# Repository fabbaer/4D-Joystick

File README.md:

# 4D-Joystick

## Introduction
The 4D-Joystick allows people with physical disabilities to control complex RC-toys, like plains or multicopper. The RC-toys are controlled via a mouthpiece, a pressure sensor and movements of the head.

The system is divided into two units. The joystickunit is the user interface. It records the user inputs, processes them and forwards them to the remoteunit. The remoteunit is responsible for the communication with the RC-toy.

### Joystickunit
The joystickunit is the main part of the system and handles all user interactions. The heart of the system is a self-developed hardware with a Cortex-M4-Controller. The firmware offers a command-line-interface (CLI) via a USB connection to configure the system. Up to 32 different configurations can be stored on the joystickunit, each offering a flexible mapping of all inputs and outputs and configurations like deadzones. 

The joystickunit can either be powered via USB or via the remoteunit. All peripherals are placed inside a 3D-printed enclosure, which can be mounted on a stand. On the outside of the housing a display and a rotary button is placed, which can be used to load different configurations and display system information. Additionally, there are four headphone jacks to connect external buttons, which can be used to control the digital channels of the remote control. The buttons can be chosen to fit the user's needs and can for example be pressed with a foot or finger. 

The analogue channels are controlled via a mouthpiece. Three of the four degrees of freedom are controlled via movements of the head in up, down, left, right, forward and backward direction. The fourth degree of freedom is controlled via a pressure sensor, which is connected to the mouthpiece. 

The firmware of the joystickunit is designed to be future-proof. In future applications, the joystickunit can for example be used as an input device for a computer or a game console. However, none of these applications are currently implemented, but many parts of the firmware are designed that this can be easily done in future. 

### Remoteunit
The remoteunit handles the communication with the RC-toy. A conventional RC-toy-remote (FrSky Taranis X9D Plus v2019) with OpenTX as main firmware is used as a basis for this unit.

The joystickunit needs to gain control over the input-devices of the remote-control (joysticks and buttons). Therefore, an additional PCB is added to the remote, which is placed right between the input devices and the main controller board. It is able to read the input-devices and control the corresponding inputs of the main controller board. Additionally, it is able to communicate with the joystickunit via SPI.

If the joystick unit is connected to this hardware, the board samples the input devices and sends this data to the joystick unit, where it can be used as input data. Parallel to this, the joystick unit sends the data for the output channels, which are then set by the board accordingly. Therefore, the joystick unit gains full access over the inputs of the remote unit.

If the joystick unit is not connected to the remoteunit, the additional board acts transparent and copies the inputs directly to the outputs. Therefore, the remote control can be normally used without the joystick unit.

## Content
### Folder "firmware"
Contains the firmware of the joystickunit and the remoteunit. Both firmwares were originally developed in STM32CubeIDE. The corresponding project files for this IDE were also included in this directory. 

To flash the firmware to the units a JTAG-programmer (e.g. ST-Link) and an adapter (e.g. Olimex ARM-JTAG-20-10) is needed.
 
### Folder "hardware"
Contains the hardware for both units. The PCBs were developed in Autodesk EAGLE. However, the folder contains also a PDF of the schematics and GERBER-data for manufacturing.

**NOTE:** The bill of material can be found in the documentation-folder.

### Folder "mechanics"

Contains the 3D-models of the enclosure for the joystickunit, which can be printed with a 3D-printer. They were developed in Autodesk Fusion 360.

### Folder "documentation"
Contains a bill of material and some additional documentation for the system.

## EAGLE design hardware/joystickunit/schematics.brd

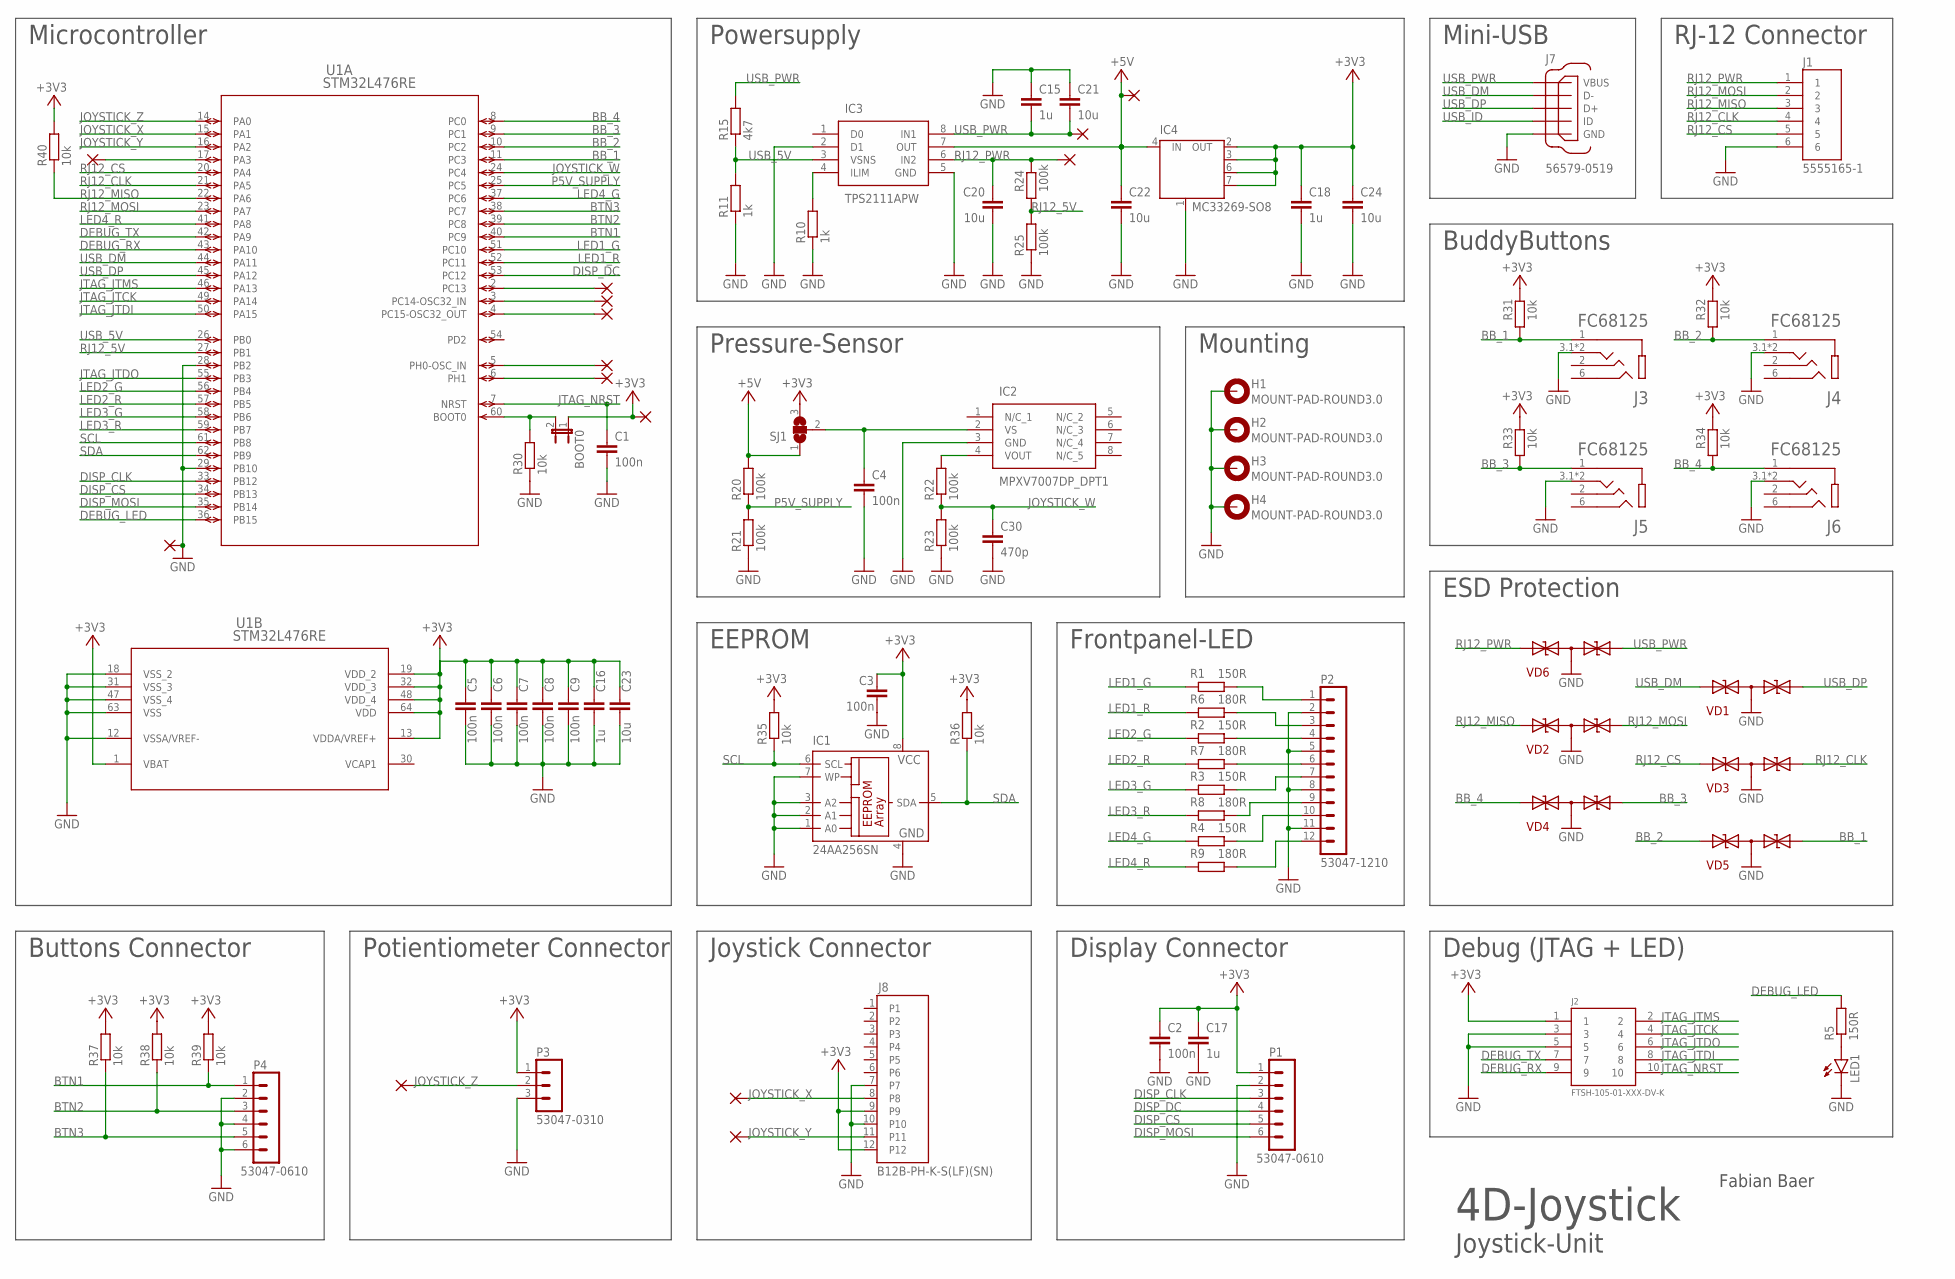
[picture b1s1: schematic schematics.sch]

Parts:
BOOT0: JP1E; JP1
C1, C2, C3, C4, C5, C6, C7, C8, C9: 100n; C0603
C15, C16, C17, C18: 1u; C0603
C20, C21, C22, C23, C24: 10u; C0603
C30: 470p; C0603
H1, H2, H3, H4: MOUNT-PAD-ROUND3.0; 3,0-PAD
IC1: 24AA256SN; SO-08
IC2: MPXV7007DP_DPT1; MPXV7007DPDPT1
IC3: TPS2111APW; SOP65P640X120-8N
IC4: MC33269-SO8; SO08
J1: 5555165-1; TE_5555165-1
J2: FTSH-105-01-XXX-DV-K
J3, J4, J5, J6: FC68125; CLIFF_FC68125
J7: 56579-0519; MOLEX_56579-0519
J8: B12B-PH-K-S(LF)(SN); JST_B12B-PH-K-S(LF)(SN)
LED1: LEDSML0603; SML0603
P1, P4: 53047-0610
P2: 53047-1210
P3: 53047-0310
PAD1, PAD2, PAD3, PAD4, PAD5, PAD6, PAD7, PAD8, PAD9, PAD10, PAD11, PAD12, PAD13, PAD14: WIREPAD1,6/0,9; 1,6/0,9
R1, R2, R3, R4, R5: 150R; R0603
R6, R7, R8, R9: 180R; R0603
R10, R11: 1k; R0603
R15: 4k7; R0603
R20, R21, R22, R23, R24, R25: 100k; R0603
R30, R31, R32, R33, R34, R35, R36, R37, R38, R39, R40: 10k; R0603
SJ1: SJ2W; SJ_2
U1: STM32L476RE; LQFP64-10X10MM
VD1, VD2, VD3, VD4, VD5, VD6: PGB102ST23WR; SOT23

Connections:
+3V3: BOOT0.1, C2.1, C3.1, C5.1, C6.1, C7.1, C8.1, C9.1, C16.1, C17.1, C18.1, C23.1, C24.1, IC1.8 (VCC), IC4.2 (OUT), IC4.3 (OUT), IC4.6 (OUT), IC4.7 (OUT), J2.1, J8.9, J8.12, P1.1, P3.1, PAD7.1, R31.2, R32.2, R33.2, R34.2, R35.2, R36.2, R37.2, R38.2, R39.2, R40.2, SJ1.3, U1.1 (VBAT), U1.13 (VDDA/VREF+), U1.19 (VDD_2), U1.32 (VDD_3), U1.48 (VDD_4), U1.64 (VDD)
+5V: C22.1, IC3.7 (OUT), IC4.4 (IN), PAD9.1, R20.2, SJ1.1
BB_1: J3.1 (1S), R31.1, U1.11 (PC3), VD5.1 (A)
BB_2: J4.1 (1S), R32.1, U1.10 (PC2), VD5.2 (A1)
BB_3: J5.1 (1S), R33.1, U1.9 (PC1), VD4.1 (A)
BB_4: J6.1 (1S), R34.1, U1.8 (PC0), VD4.2 (A1)
BTN1: P4.1, R39.1, U1.40 (PC9)
BTN2: P4.3, R38.1, U1.39 (PC8)
BTN3: P4.5, R37.1, U1.38 (PC7)
DEBUG_LED: R5.2, U1.36 (PB15)
DEBUG_RX: J2.9, U1.43 (PA10)
DEBUG_TX: J2.7, U1.42 (PA9)
DISP_CLK: P1.3, U1.33 (PB12)
DISP_CS: P1.5, U1.34 (PB13)
DISP_DC: P1.4, U1.53 (PC12)
DISP_MOSI: P1.6, U1.35 (PB14)
GND: C1.2, C2.2, C3.2, C4.2, C5.2, C6.2, C7.2, C8.2, C9.2, C15.1, C16.2, C17.2, C18.2, C20.2, C21.1, C22.2, C23.2, C24.2, C30.2, H1.B3,0, H2.B3,0, H3.B3,0, H4.B3,0, IC1.1 (A0), IC1.2 (A1), IC1.3 (A2), IC1.4 (GND), IC1.7 (WP), IC2.3 (GND), IC3.2 (D1), IC3.5 (GND), IC4.1 (GND/ADJ), J1.6, J2.3, J2.5, J3.3.1 (3T), J3.3.2 (3T), J4.3.1 (3T), J4.3.2 (3T), J5.3.1 (3T), J5.3.2 (3T), J6.3.1 (3T), J6.3.2 (3T), J7.5 (GND), J8.7, J8.10, LED1.C, P1.2, P2.2, P2.5, P2.8, P2.11, P3.3, P4.2, P4.4, P4.6, PAD8.1, R10.1, R11.1, R21.1, R23.1, R25.1, R30.1, U1.12 (VSSA/VREF-), U1.18 (VSS_2), U1.28 (PB2), U1.29 (PB10), U1.31 (VSS_3), U1.47 (VSS_4), U1.63 (VSS), VD1.3 (C), VD2.3 (C), VD3.3 (C), VD4.3 (C), VD5.3 (C), VD6.3 (C)
JOYSTICK_W: C30.1, R22.1, R23.2, U1.24 (PC4)
JOYSTICK_X: J8.8, PAD12.1, U1.15 (PA1)
JOYSTICK_Y: J8.11, PAD13.1, U1.16 (PA2)
JOYSTICK_Z: P3.2, PAD14.1, U1.14 (PA0)
JTAG_JTCK: J2.4, U1.49 (PA14)
JTAG_JTDI: J2.8, U1.50 (PA15)
JTAG_JTDO: J2.6, U1.55 (PB3)
JTAG_JTMS: J2.2, U1.46 (PA13)
JTAG_NRST: C1.1, J2.10, U1.7 (NRST)
LED1_G: R1.2, U1.51 (PC10)
LED1_R: R6.2, U1.52 (PC11)
LED2_G: R2.2, U1.56 (PB4)
LED2_R: R7.2, U1.57 (PB5)
LED3_G: R3.2, U1.58 (PB6)
LED3_R: R8.2, U1.59 (PB7)
LED4_G: R4.2, U1.37 (PC6)
LED4_R: R9.2, U1.41 (PA8)
unnamed: BOOT0.2, R30.2, U1.60 (BOOT0)
unnamed: C4.1, IC2.2 (VS), SJ1.2
unnamed: IC2.4 (VOUT), R22.2
unnamed: LED1.A, R5.1
unnamed: PAD1.1, U1.6 (PH1)
unnamed: PAD2.1, U1.5 (PH0-OSC_IN)
unnamed: PAD3.1, U1.2 (PC13)
unnamed: PAD4.1, U1.3 (PC14-OSC32_IN)
unnamed: IC3.4 (ILIM), R10.2
unnamed: P2.12, R9.1
unnamed: PAD5.1, U1.4 (PC15-OSC32_OUT)
unnamed: P2.10, R4.1
unnamed: P2.9, R8.1
unnamed: P2.7, R3.1
unnamed: P2.6, R7.1
unnamed: P2.4, R2.1
unnamed: P2.3, R6.1
unnamed: P2.1, R1.1
unnamed: PAD6.1, U1.17 (PA3)
P5V_SUPPLY: R20.1, R21.2, U1.25 (PC5)
RJ12_5V: R24.1, R25.2, U1.27 (PB1)
RJ12_CLK: J1.4, U1.21 (PA5), VD3.1 (A)
RJ12_CS: J1.5, U1.20 (PA4), VD3.2 (A1)
RJ12_MISO: J1.3, R40.1, U1.22 (PA6), VD2.2 (A1)
RJ12_MOSI: J1.2, U1.23 (PA7), VD2.1 (A)
RJ12_PWR: C20.1, IC3.6 (IN2), J1.1, PAD11.1, R24.2, VD6.2 (A1)
SCL: IC1.6 (SCL), R35.1, U1.61 (PB8)
SDA: IC1.5 (SDA), R36.1, U1.62 (PB9)
USB_5V: IC3.3 (VSNS), R11.2, R15.1, U1.26 (PB0)
USB_DM: J7.2 (D-), U1.44 (PA11), VD1.2 (A1)
USB_DP: J7.3 (D+), U1.45 (PA12), VD1.1 (A)
USB_ID: J7.4 (ID)
USB_PWR: C15.2, C21.2, IC3.8 (IN1), J7.1 (VBUS), PAD10.1, R15.2, VD6.1 (A)
VCAP1: U1.30 (VCAP1)

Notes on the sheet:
Mini-USB
Debug (JTAG + LED)
RJ-12 Connector
BuddyButtons
EEPROM
Pressure-Sensor
4D-Joystick
Joystick-Unit
Fabian Baer
Microcontroller
Potientiometer Connector
Joystick Connector
Frontpanel-LED
Powersupply
Display Connector
Buttons Connector
ESD Protection
Mounting

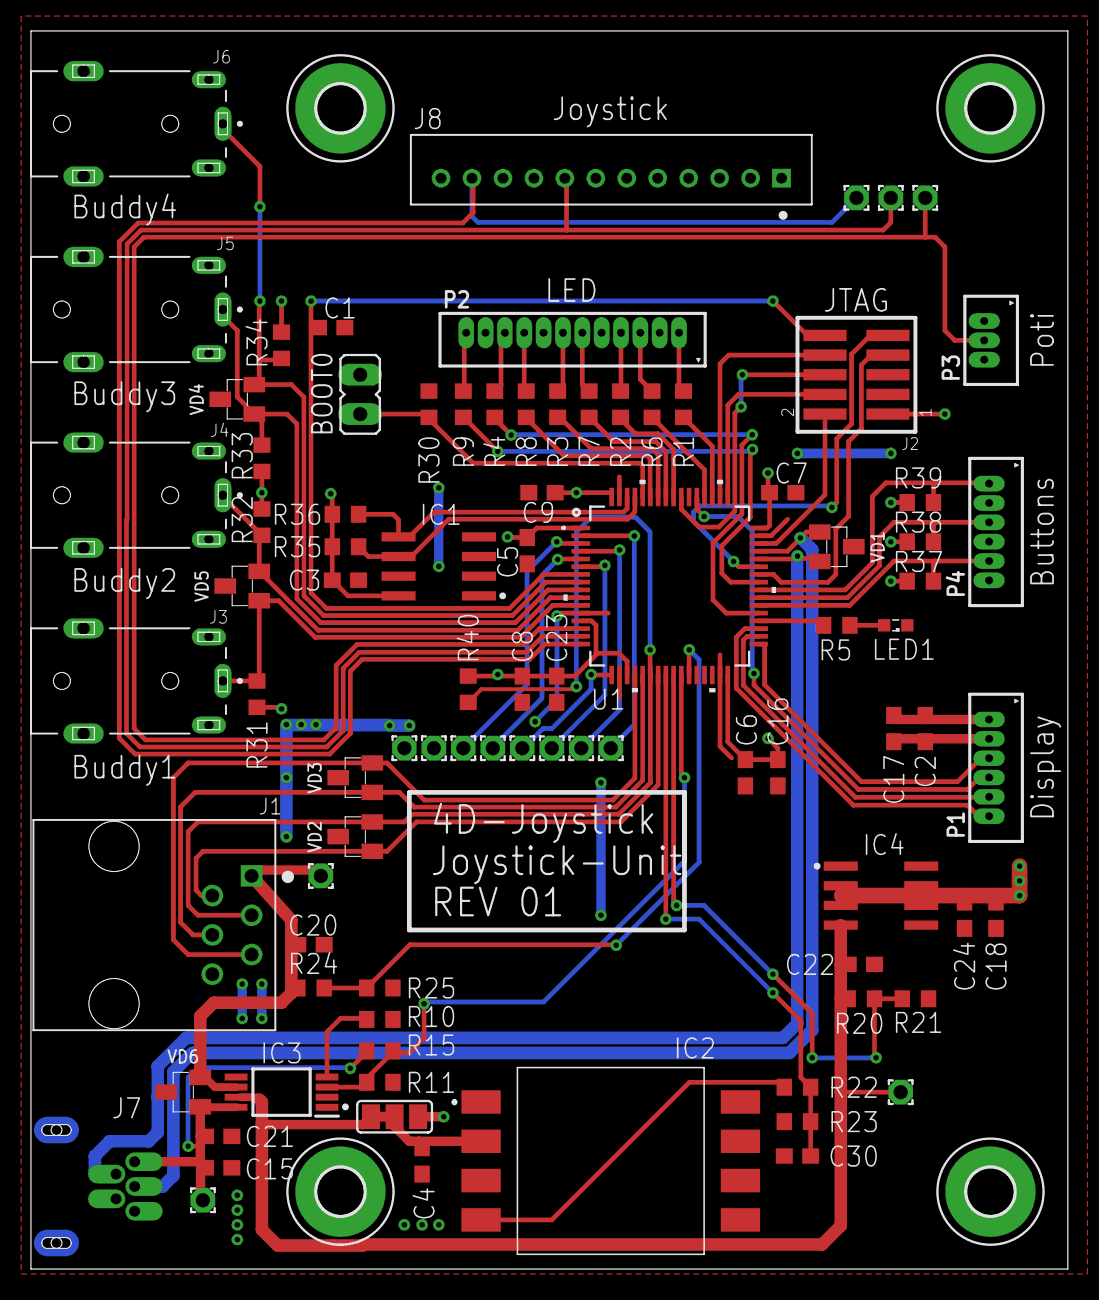
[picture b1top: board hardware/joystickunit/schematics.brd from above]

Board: 2 copper layers, 67.0 x 80.0 mm, 92 parts (0 on the bottom side), 66 nets.

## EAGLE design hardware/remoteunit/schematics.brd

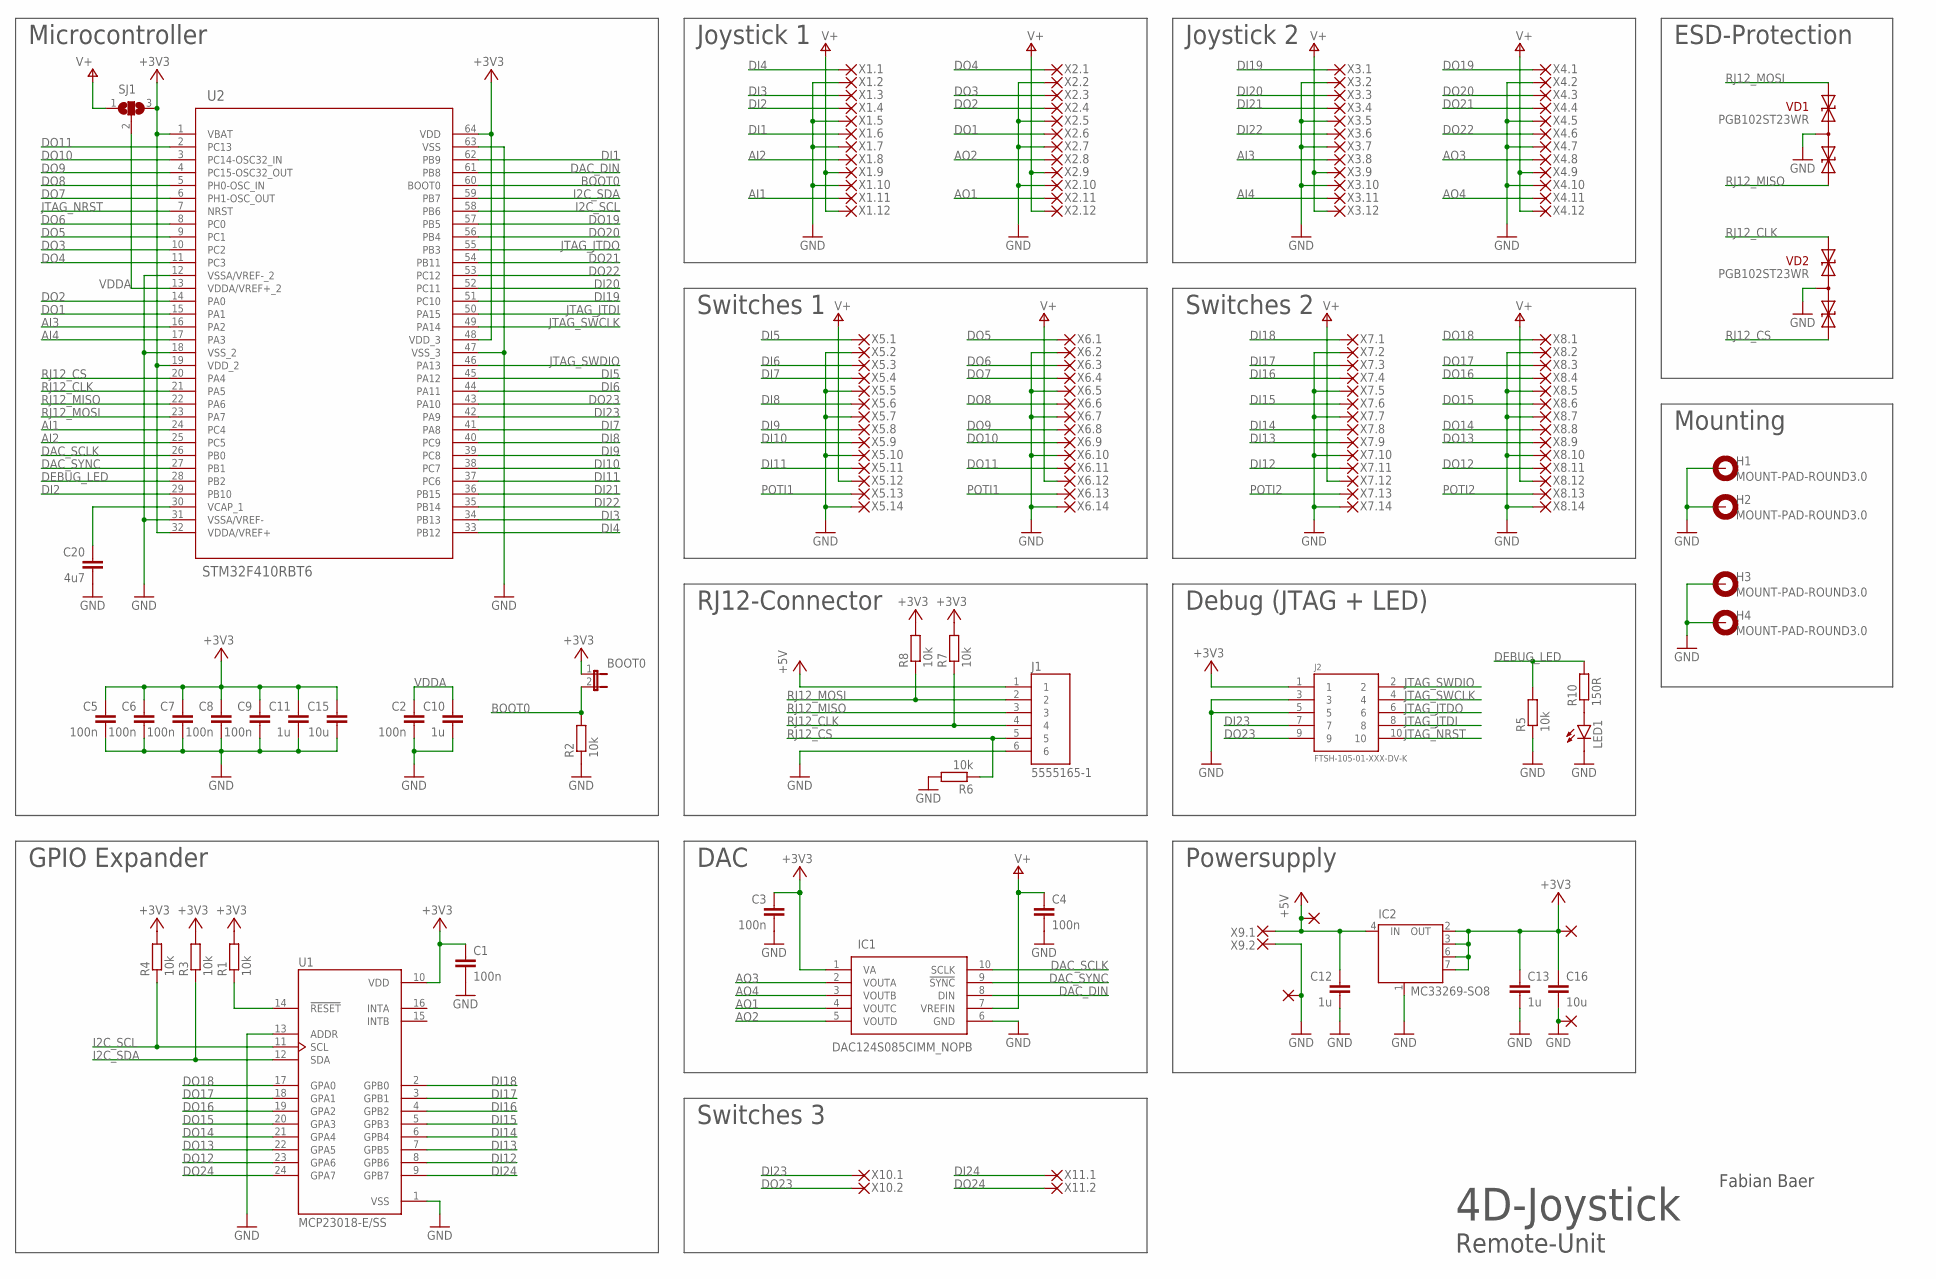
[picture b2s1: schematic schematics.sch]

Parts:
BOOT0: JP1E; JP1
C1, C2, C3, C4, C5, C6, C7, C8, C9: 100n; C0603
C10, C11, C12, C13: 1u; C0603
C15, C16: 10u; C0603
C20: 4u7; C0603
H1, H2, H3, H4: MOUNT-PAD-ROUND3.0; 3,0-PAD
IC1: DAC124S085CIMM_NOPB; SOP50P490X110-10N
IC2: MC33269-SO8; SO08
J1: 5555165-1; TE_5555165-1
J2: FTSH-105-01-XXX-DV-K
LED1: LEDSML0603; SML0603
R1, R2, R3, R4, R5, R6, R7, R8: 10k; R0603
R10: 150R; R0603
SJ1: SJ2W; SJ_2
U1: MCP23018-E/SS; SOP65P780X200-24N
U2: STM32F410RBT6; LQFP64-10X10MM
VD1, VD2: PGB102ST23WR; SOT23
X1.1, X1.2, X1.3, X1.4, X1.5, X1.6, X1.7, X1.8, X1.9, X1.10, X1.11, X1.12, X2.1, X2.2, X2.3, X2.4, X2.5, X2.6, X2.7, X2.8, X2.9, X2.10, X2.11, X2.12, X3.1, X3.2, X3.3, X3.4, X3.5, X3.6, X3.7, X3.8, X3.9, X3.10, X3.11, X3.12, X4.1, X4.2, X4.3, X4.4, X4.5, X4.6, X4.7, X4.8, X4.9, X4.10, X4.11, X4.12, X5.1, X5.2, X5.3, X5.4, X5.5, X5.6, X5.7, X5.8, X5.9, X5.10, X5.11, X5.12, X5.13, X5.14, X5.15, X5.16, X5.17, X5.18, X6.1, X6.2, X6.3, X6.4, X6.5, X6.6, X6.7, X6.8, X6.9, X6.10, X6.11, X6.12, X6.13, X6.14, X7.1, X7.2, X7.3, X7.4, X7.5, X7.6, X7.7, X7.8, X7.9, X7.10, X7.11, X7.12, X7.13, X7.14, X8.1, X8.2, X8.3, X8.4, X8.5, X8.6, X8.7, X8.8, X8.9, X8.10, X8.11, X8.12, X8.13, X8.14, X10.1, X10.2, X11.1, X11.2: WIREPAD1,6/0,9; 1,6/0,9
X9.1, X9.2: WIREPAD2,54/1,0; 2,54/1,0

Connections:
+3V3: BOOT0.1, C1.1, C3.1, C5.1, C6.1, C7.1, C8.1, C9.1, C11.1, C13.1, C15.1, C16.1, IC1.1 (VA), IC2.2 (OUT), IC2.3 (OUT), IC2.6 (OUT), IC2.7 (OUT), J2.1, R1.2, R3.2, R4.2, R7.2, R8.2, SJ1.3, U1.10 (VDD), U2.1 (VBAT), U2.19 (VDD_2), U2.32 (VDDA/VREF+), U2.48 (VDD_3), U2.64 (VDD), X5.15.1
+5V: C12.1, IC2.4 (IN), J1.1, X5.17.1, X9.1.1
AI1: U2.24 (PC4), X1.11.1
AI2: U2.25 (PC5), X1.8.1
AI3: U2.16 (PA2), X3.8.1
AI4: U2.17 (PA3), X3.11.1
AO1: IC1.4 (VOUTC), X2.11.1
AO2: IC1.5 (VOUTD), X2.8.1
AO3: IC1.2 (VOUTA), X4.8.1
AO4: IC1.3 (VOUTB), X4.11.1
BOOT0: BOOT0.2, R2.2, U2.60 (BOOT0)
DAC_DIN: IC1.8 (DIN), U2.61 (PB8)
DAC_SCLK: IC1.10 (SCLK), U2.26 (PB0)
DAC_SYNC: IC1.9 (!SYNC), U2.27 (PB1)
DEBUG_LED: R5.2, R10.2, U2.28 (PB2)
DI1: U2.62 (PB9), X1.6.1
DI2: U2.29 (PB10), X1.4.1
DI3: U2.34 (PB13), X1.3.1
DI4: U2.33 (PB12), X1.1.1
DI5: U2.45 (PA12), X5.1.1
DI6: U2.44 (PA11), X5.3.1
DI7: U2.41 (PA8), X5.4.1
DI8: U2.40 (PC9), X5.6.1
DI9: U2.39 (PC8), X5.8.1
DI10: U2.38 (PC7), X5.9.1
DI11: U2.37 (PC6), X5.11.1
DI12: U1.8 (GPB6), X7.11.1
DI13: U1.7 (GPB5), X7.9.1
DI14: U1.6 (GPB4), X7.8.1
DI15: U1.5 (GPB3), X7.6.1
DI16: U1.4 (GPB2), X7.4.1
DI17: U1.3 (GPB1), X7.3.1
DI18: U1.2 (GPB0), X7.1.1
DI19: U2.51 (PC10), X3.1.1
DI20: U2.52 (PC11), X3.3.1
DI21: U2.36 (PB15), X3.4.1
DI22: U2.35 (PB14), X3.6.1
DI23: J2.7, U2.42 (PA9), X10.1.1
DI24: U1.9 (GPB7), X11.1.1
DO1: U2.15 (PA1), X2.6.1
DO2: U2.14 (PA0), X2.4.1
DO3: U2.10 (PC2), X2.3.1
DO4: U2.11 (PC3), X2.1.1
DO5: U2.9 (PC1), X6.1.1
DO6: U2.8 (PC0), X6.3.1
DO7: U2.6 (PH1-OSC_OUT), X6.4.1
DO8: U2.5 (PH0-OSC_IN), X6.6.1
DO9: U2.4 (PC15-OSC32_OUT), X6.8.1
DO10: U2.3 (PC14-OSC32_IN), X6.9.1
DO11: U2.2 (PC13), X6.11.1
DO12: U1.23 (GPA6), X8.11.1
DO13: U1.22 (GPA5), X8.9.1
DO14: U1.21 (GPA4), X8.8.1
DO15: U1.20 (GPA3), X8.6.1
DO16: U1.19 (GPA2), X8.4.1
DO17: U1.18 (GPA1), X8.3.1
DO18: U1.17 (GPA0), X8.1.1
DO19: U2.57 (PB5), X4.1.1
DO20: U2.56 (PB4), X4.3.1
DO21: U2.54 (PB11), X4.4.1
DO22: U2.53 (PC12), X4.6.1
DO23: J2.9, U2.43 (PA10), X10.2.1
DO24: U1.24 (GPA7), X11.2.1
GND: C1.2, C2.2, C3.2, C4.2, C5.2, C6.2, C7.2, C8.2, C9.2, C10.2, C11.2, C12.2, C13.2, C15.2, C16.2, C20.2, H1.B3,0, H2.B3,0, H3.B3,0, H4.B3,0, IC1.6 (GND), IC2.1 (GND/ADJ), J1.6, J2.3, J2.5, LED1.C, R2.1, R5.1, R6.2, U1.1 (VSS), U1.13 (ADDR), U2.12 (VSSA/VREF-_2), U2.18 (VSS_2), U2.31 (VSSA/VREF-), U2.47 (VSS_3), U2.63 (VSS), VD1.3 (C), VD2.3 (C), X1.2.1, X1.5.1, X1.7.1, X1.10.1, X2.2.1, X2.5.1, X2.7.1, X2.10.1, X3.2.1, X3.5.1, X3.7.1, X3.10.1, X4.2.1, X4.5.1, X4.7.1, X4.10.1, X5.2.1, X5.5.1, X5.7.1, X5.10.1, X5.14.1, X5.16.1, X5.18.1, X6.2.1, X6.5.1, X6.7.1, X6.10.1, X6.14.1, X7.2.1, X7.5.1, X7.7.1, X7.10.1, X7.14.1, X8.2.1, X8.5.1, X8.7.1, X8.10.1, X8.14.1, X9.2.1
I2C_SCL: R4.1, U1.11 (SCL), U2.58 (PB6)
I2C_SDA: R3.1, U1.12 (SDA), U2.59 (PB7)
JTAG_JTDI: J2.8, U2.50 (PA15)
JTAG_JTDO: J2.6, U2.55 (PB3)
JTAG_NRST: J2.10, U2.7 (NRST)
JTAG_SWCLK: J2.4, U2.49 (PA14)
JTAG_SWDIO: J2.2, U2.46 (PA13)
unnamed: R1.1, U1.14 (!RESET)
unnamed: C20.1, U2.30 (VCAP_1)
unnamed: LED1.A, R10.1
POTI1: X5.13.1, X6.13.1
POTI2: X7.13.1, X8.13.1
RJ12_CLK: J1.4, R7.1, U2.21 (PA5), VD2.2 (A1)
RJ12_CS: J1.5, R6.1, U2.20 (PA4), VD2.1 (A)
RJ12_MISO: J1.3, U2.22 (PA6), VD1.1 (A)
RJ12_MOSI: J1.2, R8.1, U2.23 (PA7), VD1.2 (A1)
V+: C4.1, IC1.7 (VREFIN), SJ1.1, X1.9.1, X1.12.1, X2.9.1, X2.12.1, X3.9.1, X3.12.1, X4.9.1, X4.12.1, X5.12.1, X6.12.1, X7.12.1, X8.12.1
VDDA: C2.1, C10.1, SJ1.2, U2.13 (VDDA/VREF+_2)

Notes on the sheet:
Microcontroller
Debug (JTAG + LED)
4D-Joystick
Remote-Unit
Fabian Baer
ESD-Protection
Powersupply
DAC
Joystick 1
Joystick 2
GPIO Expander
Switches 1
Switches 2
Mounting
Switches 3
RJ12-Connector

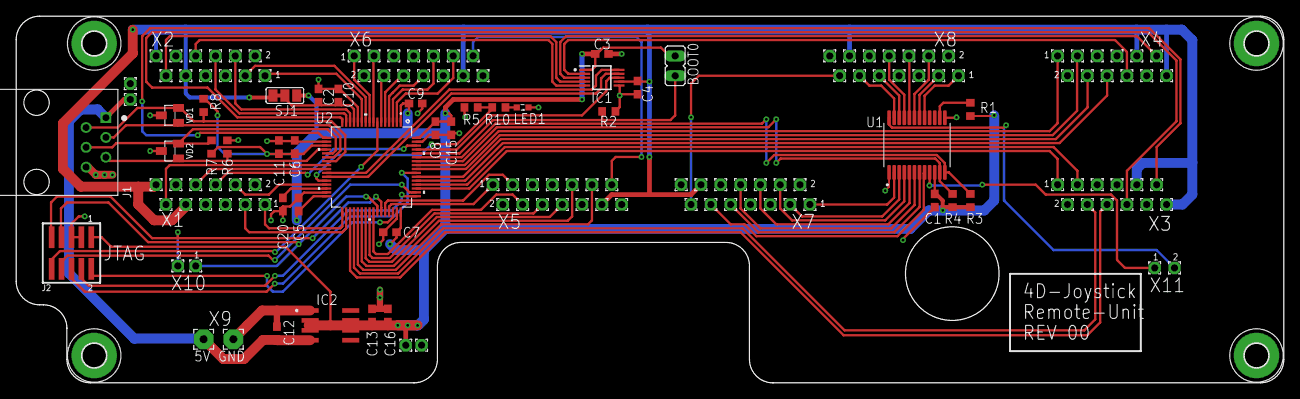
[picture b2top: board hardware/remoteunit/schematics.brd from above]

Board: 2 copper layers, 162.5 x 47.0 mm, 154 parts (0 on the bottom side), 82 nets.

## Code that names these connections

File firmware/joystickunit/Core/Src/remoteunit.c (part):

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    {LED3_G_Port, LED3_R_Port},
    {LED4_G_Port, LED4_R_Port}};
static uint16_t const buddyButtons_ledPins[4][2] = {
    {LED1_G_Pin, LED1_R_Pin},
    {LED2_G_Pin, LED2_R_Pin},
    {LED3_G_Pin, LED3_R_Pin},
    {LED4_G_Pin, LED4_R_Pin}};
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  __HAL_RCC_GPIOC_CLK_ENABLE();

  //Init SPI-Pins
  HAL_GPIO_WritePin(RJ12_CS_Port, RJ12_CS_Pin, GPIO_PIN_RESET);

  GPIO_InitStruct.Pin = RJ12_CS_Pin;
  GPIO_InitStruct.Mode = GPIO_MODE_OUTPUT_PP;
  GPIO_InitStruct.Pull = GPIO_NOPULL;
  GPIO_InitStruct.Speed = GPIO_SPEED_FREQ_LOW;
  HAL_GPIO_Init(GPIOA, &GPIO_InitStruct);

  GPIO_InitStruct.Pin = RJ12_SCK_Pin | RJ12_MISO_Pin | RJ12_MOSI_Pin;
  GPIO_InitStruct.Mode = GPIO_MODE_AF_PP;
  GPIO_InitStruct.Pull = GPIO_NOPULL;
  GPIO_InitStruct.Speed = GPIO_SPEED_FREQ_VERY_HIGH;
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  HAL_GPIO_Init(GPIOA, &GPIO_InitStruct);

  //Init LED-Pins
  HAL_GPIO_WritePin(GPIOB, LED2_G_Pin | LED2_R_Pin | LED3_G_Pin | LED3_R_Pin, GPIO_PIN_RESET);
  HAL_GPIO_WritePin(GPIOC, LED4_G_Pin | LED1_G_Pin | LED1_R_Pin, GPIO_PIN_RESET);
  HAL_GPIO_WritePin(GPIOA, LED4_R_Pin, GPIO_PIN_RESET);

  GPIO_InitStruct.Pin = LED4_R_Pin;
  GPIO_InitStruct.Mode = GPIO_MODE_OUTPUT_PP;
  GPIO_InitStruct.Pull = GPIO_NOPULL;
  GPIO_InitStruct.Speed = GPIO_SPEED_FREQ_LOW;
  HAL_GPIO_Init(GPIOA, &GPIO_InitStruct);

  GPIO_InitStruct.Pin = LED2_G_Pin | LED2_R_Pin | LED3_G_Pin | LED3_R_Pin;
  GPIO_InitStruct.Mode = GPIO_MODE_OUTPUT_PP;
  GPIO_InitStruct.Pull = GPIO_NOPULL;
  GPIO_InitStruct.Speed = GPIO_SPEED_FREQ_LOW;
  HAL_GPIO_Init(GPIOB, &GPIO_InitStruct);

  GPIO_InitStruct.Pin = LED4_G_Pin | LED1_G_Pin | LED1_R_Pin;
  GPIO_InitStruct.Mode = GPIO_MODE_OUTPUT_PP;
  GPIO_InitStruct.Pull = GPIO_NOPULL;
  GPIO_InitStruct.Speed = GPIO_SPEED_FREQ_LOW;
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  uint8_t rxData[10], txData[10];

  //Enable Remote-Unit
  HAL_GPIO_WritePin(RJ12_CS_Port, RJ12_CS_Pin, GPIO_PIN_SET);

  //Disable all flags
  flag_reloadConfig = false;
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
    //Communicate with remoteunit
    if(system_isRemoteConnected()) {
      HAL_GPIO_WritePin(RJ12_CS_Port, RJ12_CS_Pin, GPIO_PIN_RESET);
      remUnit_packData(&ioStates, txData);
      if (HAL_SPI_TransmitReceive(&hspi1, txData, rxData, 10, 10) == HAL_ERROR) {
        system_errorHandler();
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      if(remUnit_checkCRC(rxData, 9)) {
        remUnit_unpackData(&ioStates, rxData);
      }
      HAL_GPIO_WritePin(RJ12_CS_Port, RJ12_CS_Pin, GPIO_PIN_SET);
    }

    //Handle flags
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    }

    if(flag_terminateTask) {
      HAL_GPIO_WritePin(RJ12_CS_Port, RJ12_CS_Pin, GPIO_PIN_RESET);
      remUnit_resetBuddyButtons(buddyStates);
      osThreadTerminate(htask_remoteunit);
      flag_teacherMode = false;
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  pStates[buddyButton4] = bbState_off;

  //Reset LEDs
  HAL_GPIO_WritePin(GPIOB, LED2_G_Pin | LED2_R_Pin | LED3_G_Pin | LED3_R_Pin, GPIO_PIN_RESET);
  HAL_GPIO_WritePin(GPIOC, LED4_G_Pin | LED1_G_Pin | LED1_R_Pin, GPIO_PIN_RESET);
  HAL_GPIO_WritePin(GPIOA, LED4_R_Pin, GPIO_PIN_RESET);

  //Empty message queue
  while(osMessageWaiting(buddyButtonsMsgBox) > 0) {
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
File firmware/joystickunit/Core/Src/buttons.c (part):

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void buttons_init( void ) {
  GPIO_InitTypeDef GPIO_InitStruct = { 0 };

  GPIO_InitStruct.Pin = BB_4_Pin | BB_3_Pin | BB_2_Pin | BB_1_Pin | BTN3_Pin
      | BTN2_Pin | BTN1_Pin;
  GPIO_InitStruct.Mode = GPIO_MODE_INPUT;
  GPIO_InitStruct.Pull = GPIO_PULLUP;
  HAL_GPIO_Init(GPIOC, &GPIO_InitStruct);
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  Button_t bb1, bb2, bb3, bb4, rotP, rot1, rot2;

  //Initialize structs
  buttons_initStruct(&bb1, 50, BB_1_Port, BB_1_Pin);
  buttons_initStruct(&bb2, 50, BB_2_Port, BB_2_Pin);
  buttons_initStruct(&bb3, 50, BB_3_Port, BB_3_Pin);
  buttons_initStruct(&bb4, 50, BB_4_Port, BB_4_Pin);
  buttons_initStruct(&rot1, 1, BTN2_Port, BTN2_Pin);
  buttons_initStruct(&rot2, 1, BTN3_Port, BTN3_Pin);
  buttons_initStruct(&rotP, 1, BTN1_Port, BTN1_Pin);

  while(1) {
    buttons_handleBuddyButton(&bb1, buddyButton1);
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

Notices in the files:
parts and their libraries:
molex_microblade: Copyright (C) 2010, Bob Starr
